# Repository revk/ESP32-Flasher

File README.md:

# ESP32-Flasher

Now at [Codeberg](https://codeberg.org/RevK/ESP32-Flasher)

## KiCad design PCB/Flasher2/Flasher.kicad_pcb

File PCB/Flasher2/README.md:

# Flasher2

## Trademark

This project is subject to the licence in the LICENCE file, and even if that says it is an open source project, you cannot sell boards or cases bearing the Andrews & Arnold Ltd name, the A&A logo, the registered trademark AJK logo or other registered trademarks, or any GS1 allocated EANs/barcode assigned to Andrews & Arnold Ltd.

## PCB Designs

These files are for use with [KiCAD](https://www.kicad.org).

- [Flasher](Flasher.kicad_pro)

## 3D

3D case designs are normally automatically created from the PCB so as to ensure correct details and placement of apertures, etc.

|Design|Bottom|Top|Combined|
|------|------|---|--------|
|Flasher||||

## PCB Images

---

*Auto generated README.md 2026-01-28T10:23:43*

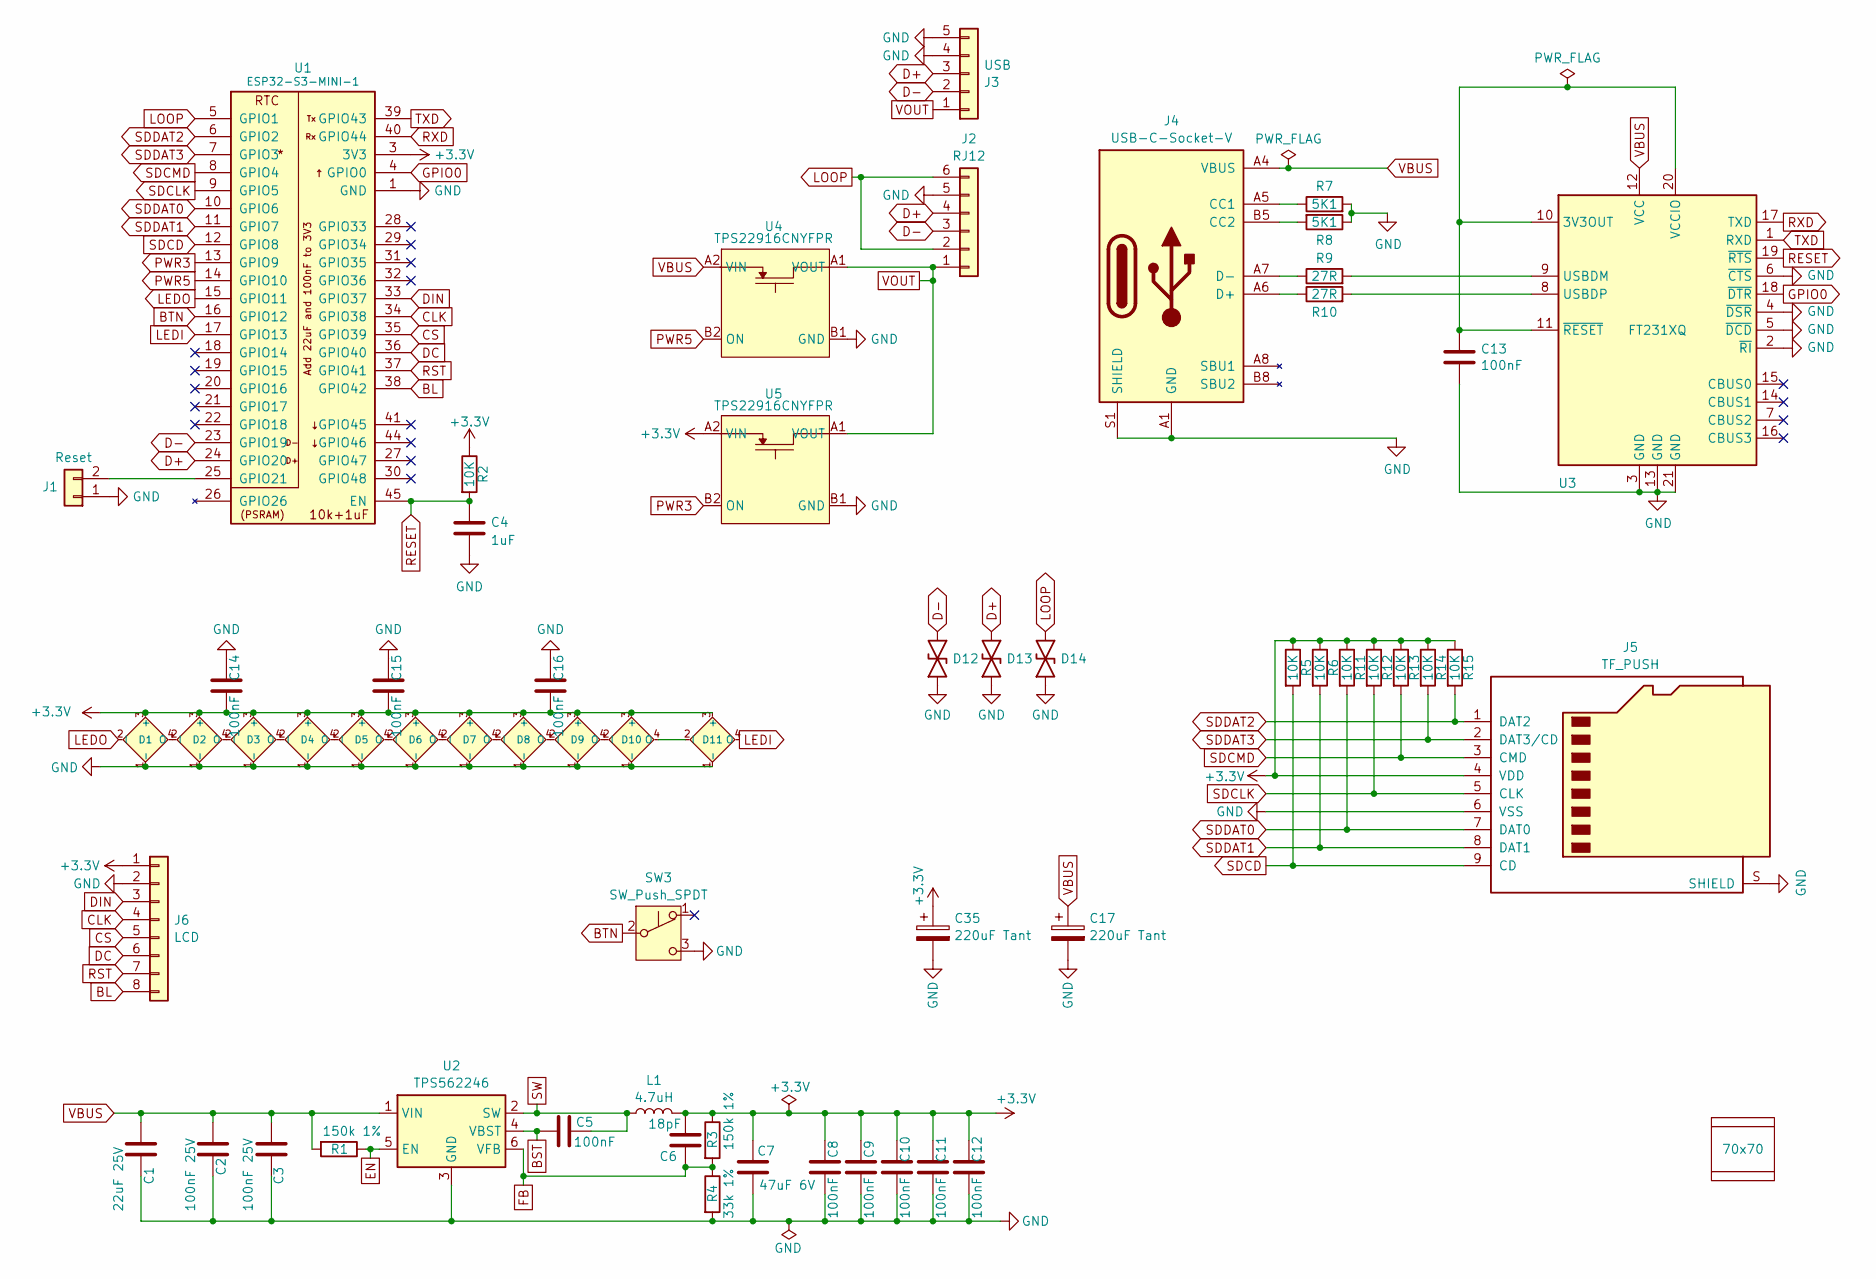
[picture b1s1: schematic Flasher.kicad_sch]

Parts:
C1: 22uF 25V; C_0805; MPN C45783
C2, C3: 100nF 25V; C_0402; MPN C56392
C4: 1uF; C_0201
C5, C8, C9, C10, C11, C12, C14, C15, C16: 100nF; C_0201; MPN C76934
C6: 18pF; C_0201; MPN C62164
C7: 47uF 6V; C_0805; MPN C16780
C13: 100nF; C_0201
C17, C35: 220uF Tant; CP_EIA-3528-21_Kemet-B; MPN C122649
D1, D2, D3, D4, D5, D6, D7, D8, D9, D10: XL-1010RGBC-WS2812B; SMD1615; MPN C5349954
D11: XL-1010RGBC-WS2812B; SMD1615-Side; MPN C5349954
D12, D13, D14: DFN1006-2L; MPN C5137770
J1: Reset; AA-Pad
J2: RJ12; RJ12_Horizontal; MPN C77859
J3: USB; USB_A_Horizontal; MPN C720525
J4: USB-C-Socket-V; USB-C-Socket-H; MPN C709357
J5: TF_PUSH; MPN C393941
J6: LCD; LCD2; MPN C42380985
L1: 4.7uH; L_5x5; MPN C307876
PCB1: 70x70; PCB7070
R1, R3: 150k 1%; R_0201; MPN C310173
R2, R5, R6, R11, R12, R13, R14, R15: 10K; R_0201; MPN C106225
R4: 33k 1%; R_0201; MPN C320835
R7, R8: 5K1; R_0201; MPN C270344
R9, R10: 27R; R_0201; MPN C273295
SW3: SW_Push_SPDT; PS-12E15; MPN C2884730
U1: ESP32-S3-MINI-1; MPN C3013941
U2: TPS562246; SOT-5x3-6; MPN C41833479
U3: FT231XQ; QFN-20-1EP_4x4mm_P0.5mm_EP2.5x2.5mm; Part No FT231XQ
U4, U5: TPS22916CNYFPR; WCSP-4-0.78x0.78; MPN C2655476
V2, V3: VCUT70N

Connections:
+3.3V: C6.2, C7.1, C8.2, C9.2, C10.2, C11.2, C12.2, C14.1, C15.1, C16.1, C35.1, D1.3 (+), D2.3 (+), D3.3 (+), D4.3 (+), D5.3 (+), D6.3 (+), D7.3 (+), D8.3 (+), D9.3 (+), D10.3 (+), D11.3 (+), J5.4 (VDD), J6.1, L1.2, R2.1, R3.1, R5.1, R6.1, R11.1, R12.1, R13.1, R14.1, R15.1, U1.3 (3V3), U5.A2 (VIN)
BL: J6.8, U1.38 (GPIO42)
BST: C5.1, U2.4 (VBST)
BTN: SW3.2 (B), U1.16 (GPIO12)
CLK: J6.4, U1.34 (GPIO38)
CS: J6.5, U1.35 (GPIO39)
D+: D13.2, J2.4, J3.3, U1.24 (GPIO20)
D-: D12.2, J2.3, J3.2, U1.23 (GPIO19)
DC: J6.6, U1.36 (GPIO40)
DIN: J6.3, U1.33 (GPIO37)
EN: R1.1, U2.5 (EN)
FB: C6.1, R3.2, R4.1, U2.6 (VFB)
GND: C1.2, C2.2, C3.2, C4.2, C7.2, C8.1, C9.1, C10.1, C11.1, C12.1, C13.2, C14.2, C15.2, C16.2, C17.2, C35.2, D1.1 (-), D2.1 (-), D3.1 (-), D4.1 (-), D5.1 (-), D6.1 (-), D7.1 (-), D8.1 (-), D9.1 (-), D10.1 (-), D11.1 (-), D12.1, D13.1, D14.1, J1.1, J2.5, J3.4, J3.5, J4.A1 (GND), J4.A12 (GND), J4.B1 (GND), J4.B12 (GND), J4.S1 (SHIELD), J5.6 (VSS), J5.S (SHIELD), J6.2, R4.2, R7.2, R8.1, SW3.3 (C), U1.1 (GND), U1.2 (GND), U1.42 (GND), U1.43 (GND), U1.46 (GND), U1.47 (GND), U1.48 (GND), U1.49 (GND), U1.50 (GND), U1.51 (GND), U1.52 (GND), U1.53 (GND), U1.54 (GND), U1.55 (GND), U1.56 (GND), U1.57 (GND), U1.58 (GND), U1.59 (GND), U1.60 (GND), U1.61 (GND), U1.62 (GND), U1.63 (GND), U1.64 (GND), U1.65 (GND), U2.3 (GND), U3.2 (~RI), U3.3 (GND), U3.4 (~DSR), U3.5 (~DCD), U3.6 (~CTS), U3.13 (GND), U3.21 (GND), U4.B1 (GND), U5.B1 (GND)
GPIO0: U1.4 (GPIO0), U3.18 (~DTR)
LEDI: D11.4 (O), U1.17 (GPIO13)
LEDO: D1.2 (I), U1.15 (GPIO11)
LOOP: D14.2, J2.2, J2.6, U1.5 (GPIO1)
unnamed: D1.4 (O), D2.2 (I)
unnamed: D2.4 (O), D3.2 (I)
unnamed: D3.4 (O), D4.2 (I)
unnamed: D4.4 (O), D5.2 (I)
unnamed: D5.4 (O), D6.2 (I)
unnamed: D6.4 (O), D7.2 (I)
unnamed: D7.4 (O), D8.2 (I)
unnamed: D8.4 (O), D9.2 (I)
unnamed: D9.4 (O), D10.2 (I)
unnamed: D10.4 (O), D11.2 (I)
unnamed: J1.2, U1.25 (GPIO21)
unnamed: J4.A5 (CC1), R7.1
unnamed: J4.B5 (CC2), R8.2
unnamed: J4.A6 (D+), J4.B6 (D+), R10.1
unnamed: J4.A7 (D-), J4.B7 (D-), R9.1
unnamed: C13.1, U3.10 (3V3OUT), U3.11 (~RESET), U3.20 (VCCIO)
unnamed: R9.2, U3.9 (USBDM)
unnamed: R10.2, U3.8 (USBDP)
PWR3: U1.13 (GPIO9), U5.B2 (ON)
PWR5: U1.14 (GPIO10), U4.B2 (ON)
RESET: C4.1, R2.2, U1.45 (EN), U3.19 (~RTS)
RST: J6.7, U1.37 (GPIO41)
RXD: U1.40 (GPIO44), U3.17 (TXD)
SDCD: J5.9 (CD), R5.2, U1.12 (GPIO8)
SDCLK: J5.5 (CLK), R12.2, U1.9 (GPIO5)
SDCMD: J5.3 (CMD), R13.2, U1.8 (GPIO4)
SDDAT0: J5.7 (DAT0), R11.2, U1.10 (GPIO6)
SDDAT1: J5.8 (DAT1), R6.2, U1.11 (GPIO7)
SDDAT2: J5.1 (DAT2), R15.2, U1.6 (GPIO2)
SDDAT3: J5.2 (DAT3/CD), R14.2, U1.7 (GPIO3)
SW: C5.2, L1.1, U2.2 (SW)
TXD: U1.39 (GPIO43), U3.1 (RXD)
VBUS: C1.1, C2.1, C3.1, C17.1, J4.A4 (VBUS), J4.A9 (VBUS), J4.B4 (VBUS), J4.B9 (VBUS), R1.2, U2.1 (VIN), U3.12 (VCC), U4.A2 (VIN)
VOUT: J2.1, J3.1, U4.A1 (VOUT), U5.A1 (VOUT)

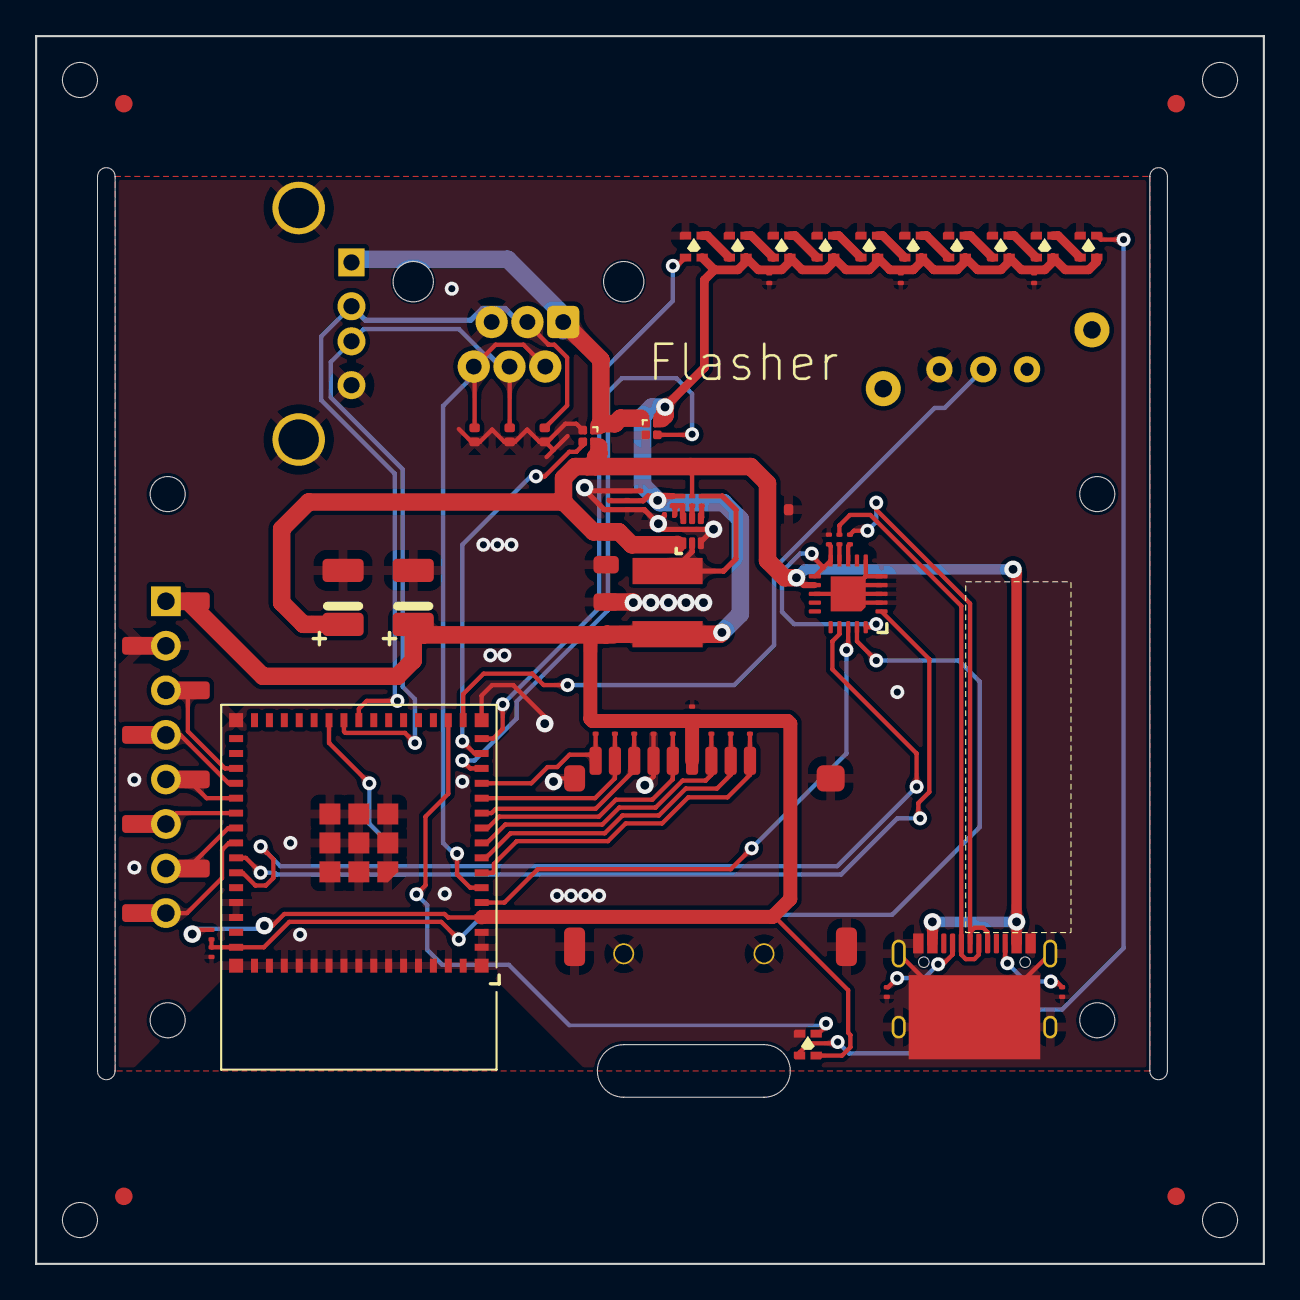
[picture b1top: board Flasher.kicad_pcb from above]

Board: 2 copper layers, 70.0 x 70.0 mm, 63 parts (1 on the bottom side), 51 nets.

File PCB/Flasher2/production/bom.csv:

Designator,Footprint,Quantity,Value,LCSC Part #
C1,C_0805,1,22uF 25V,C45783
"C10, C11, C12, C14, C15, C16, C5, C8, C9",C_0201,9,100nF,C76934
C13,C_0201,1,100nF,
"C17, C35",CP_EIA-3528-21_Kemet-B,2,220uF Tant,C122649
"C2, C3",C_0402,2,100nF 25V,C56392
C4,C_0201,1,1uF,
C6,C_0201,1,18pF,C62164
C7,C_0805,1,47uF 6V,C16780
"D1, D10, D2, D3, D4, D5, D6, D7, D8, D9",SMD1615,10,XL-1010RGBC-WS2812B,C5349954
D11,SMD1615-Side,1,XL-1010RGBC-WS2812B,C5349954
"D12, D13, D14",DFN1006-2L,3,~,C5137770
J2,RJ12_Horizontal,1,RJ12,C77859
J3,USB_A_Horizontal,1,USB,C720525
J4,USB-C-Socket-H,1,USB-C-Socket-V,C709357
J5,TF_PUSH,1,TF_PUSH,C393941
J6,LCD2,1,LCD,C42380985
L1,L_5x5,1,4.7uH,C307876
"R1, R3",R_0201,2,150k 1%,C310173
"R10, R9",R_0201,2,27R,C273295
"R11, R12, R13, R14, R15, R2, R5, R6",R_0201,8,10K,C106225
R4,R_0201,1,33k 1%,C320835
"R7, R8",R_0201,2,5K1,C270344
SW3,PS-12E15,1,SW_Push_SPDT,C2884730
U1,ESP32-S3-MINI-1,1,ESP32-S3-MINI-1,C3013941
U2,SOT-5x3-6,1,TPS562246,C41833479
U3,QFN-20-1EP_4x4mm_P0.5mm_EP2.5x2.5mm,1,FT231XQ,C132159
"U4, U5",WCSP-4-0.78x0.78,2,TPS22916CNYFPR,C2655476

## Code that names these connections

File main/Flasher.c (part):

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   {
      while (!b.die)
      {
         if (revk_gpio_get (btn))
         {
            ESP_LOGE (TAG, "Button press");
            if (b.connected)
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                  b.reload = 1;
               }
            }
            while (revk_gpio_get (btn))
               usleep (100000);
            continue;
         }
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{
   esp_err_t e = 0;
   // SD card set up
   revk_gpio_input (sdcd);
   sdmmc_card_t *card = NULL;
   sdmmc_slot_config_t slot = SDMMC_SLOT_CONFIG_DEFAULT ();
   sdmmc_host_t host = SDMMC_HOST_DEFAULT ();
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      ledsd = 'Y';
      ESP_LOGI (TAG, "Waiting SD");
      // Wait for SD card
      while (!revk_gpio_get (sdcd))
      {
         b.checked = 0;
         usleep (100000);
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            jo_string (j, "error", "Failed to initialise");
         jo_int (j, "code", e);
         revk_error ("SD", &j);
         while (revk_gpio_get (sdcd))
            usleep (100000);
         continue;
      }
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      {
         // TODO how do we do serial via UART?
         ESP_LOGE (TAG, "Power on %s", b.voltage3v3 ? "3.3V" : "5V");
         revk_gpio_output (b.voltage3v3 ? pwr3 : pwr5, 1);      // device on
         usb_host_lib_set_root_port_power (true);
         while (revk_gpio_get (sdcd) && !b.die && !b.reload && !revk_shutting_down (NULL))
         {
            b.fileerror = 0;
            if (badusb && badusb + 2 > uptime ())
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               if (!b.forceerase && b.connected && !b.reload)
               {
                  ESP_LOGE (TAG, "Wait disconnect");
                  while (revk_gpio_get (sdcd) && b.connected && !b.reload && !b.forceerase && !revk_shutting_down (NULL))
                     usleep (100000);
               }
            }
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         ESP_LOGE (TAG, "Power off");
         if (b.connected)
            usb_host_lib_set_root_port_power (false);
         revk_gpio_output (pwr3, 0);
         revk_gpio_output (pwr5, 0);
      } else
         sleep (1);
      ESP_LOGI (TAG, "Dismounting SD");
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      revk_web_settings_add (webserver);
      register_get_uri ("/", web_root);
   }
   revk_gpio_output (pwr3, 0);
   revk_gpio_output (pwr5, 0);
   revk_task ("led", led_task, NULL, 4);
#ifndef CONFIG_GFX_BUILD_SUFFIX_GFXNONE
   revk_task ("lcd", lcd_task, NULL, 4);
#endif
   revk_gpio_input (btn);
   revk_task ("btn", btn_task, NULL, 4);
   revk_task ("flash", flash_task, NULL, 16);
}
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
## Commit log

2025-09-13 Library update
2025-09-13 Starte
2025-09-13 Start PCb
2025-09-13 Parts
2025-09-13 Loop
2025-09-13 Started placement
2025-09-13 New tweaks
2025-09-14 New sockets
2025-09-14 Board ready
2025-09-14 Tidy
2025-09-16 New render
2025-09-16 Cleaner case
2025-09-18 Cleanup case
2025-09-22 Start on code
2025-09-22 Stub
2025-09-23 Beta
2025-09-23 SD and power
2025-09-23 USB started
2025-09-23 Serial connect worked - needs a lot more now.
2025-09-23 Reverse USB, FFS
2025-09-23 README
2025-09-23 State detect
2025-09-23 Not fucking workind
2025-09-24 Reset for download
2025-09-24 Started on reset logic
2025-09-24 PCB update
2025-09-24 reset cycle fixed
2025-09-24 Thicker case
2025-09-25 Loader connecting, at last, more work needed
2025-09-25 Runs once
2025-09-25 Is working to get bootloader mode, next is checking run status, and finding more info on chip
2025-09-25 Cleaner
2025-09-25 Status report on non bootloader connect now
2025-09-25 Chip name
2025-09-25 Fix dir name
2025-09-25 It works
2025-09-25 TODO
2025-09-26 ledsd
2025-09-26 More on LED options
2025-09-26 Several improvements
2025-09-26 New manifest
2025-09-26 Handle bad manifests better
2025-09-26 Bad USB connection red LED
2025-09-26 Better
2025-09-26 Upgrade files
2025-09-26 Upgrade
2025-09-26 Less flashy
2025-09-26 no point re-flashing a definite fail
2025-09-27 Release
2025-09-27 button control
2025-09-27 Better upgrade check logic and faster https
2025-09-27 Cleaner progress start
2025-09-27 LED tidy
2025-09-30 Upgrade improvements
2025-09-30 Force erase
2025-10-01 "check" and "voltage" added
2025-10-01 Re-render
2025-10-02 Sending setting
2025-10-02 Try taht
2025-10-02 Cleaner, albeit messy, settings
2025-10-03 Settings
2025-10-03 Looks good
2025-10-03 Handle PASS/FAIL quickly
2025-10-03 Change name to app
2025-10-04 Tweak settings logic
2025-10-04 Tidy for 404, etc
2025-10-04 Bug fixes
2025-10-05 Tweak messages used
2025-10-05 New ATE
2025-10-05 Clean up
2025-10-05 Fix timeout
2025-10-05 Added a load of IMPROV
2025-10-05 IMPROV
2025-10-05 Longer wait
2025-10-06 Flash and verify logic tidy
2025-10-09 LED update
2025-10-09 New LED
2025-10-12 Re render
2025-10-12 LED 3D update
2025-10-22 Render and space LEDs
2025-11-08 URLs
2025-11-08 manifest URL override settings
2025-11-08 Clears manifesturl if same as file
2025-11-08 Hash based filename
2025-11-08 Tail of url in hashed filenames to be easier to follow
2025-11-17 Unused settings, and new OTA
2025-11-17 defaults for manifest settings
2025-11-17 wording
2025-11-18 ATE wait
2025-11-18 Working on new manifest read logic
2025-11-18 Main web page
2025-11-21 fix: flasher needing reset every other board, S'Oh
2026-01-15 New lib
2026-01-16 New board design started
2026-01-17 Started Flasher 2 layout
2026-01-17 Working on case
2026-01-18 More
2026-01-19 As ordered
2026-01-26 Display logic
2026-01-26 Started on image
2026-01-26 Image
2026-01-27 Tweaks
2026-01-28 Rerender
2026-01-28 New button
2026-01-28 Minor tweaks
